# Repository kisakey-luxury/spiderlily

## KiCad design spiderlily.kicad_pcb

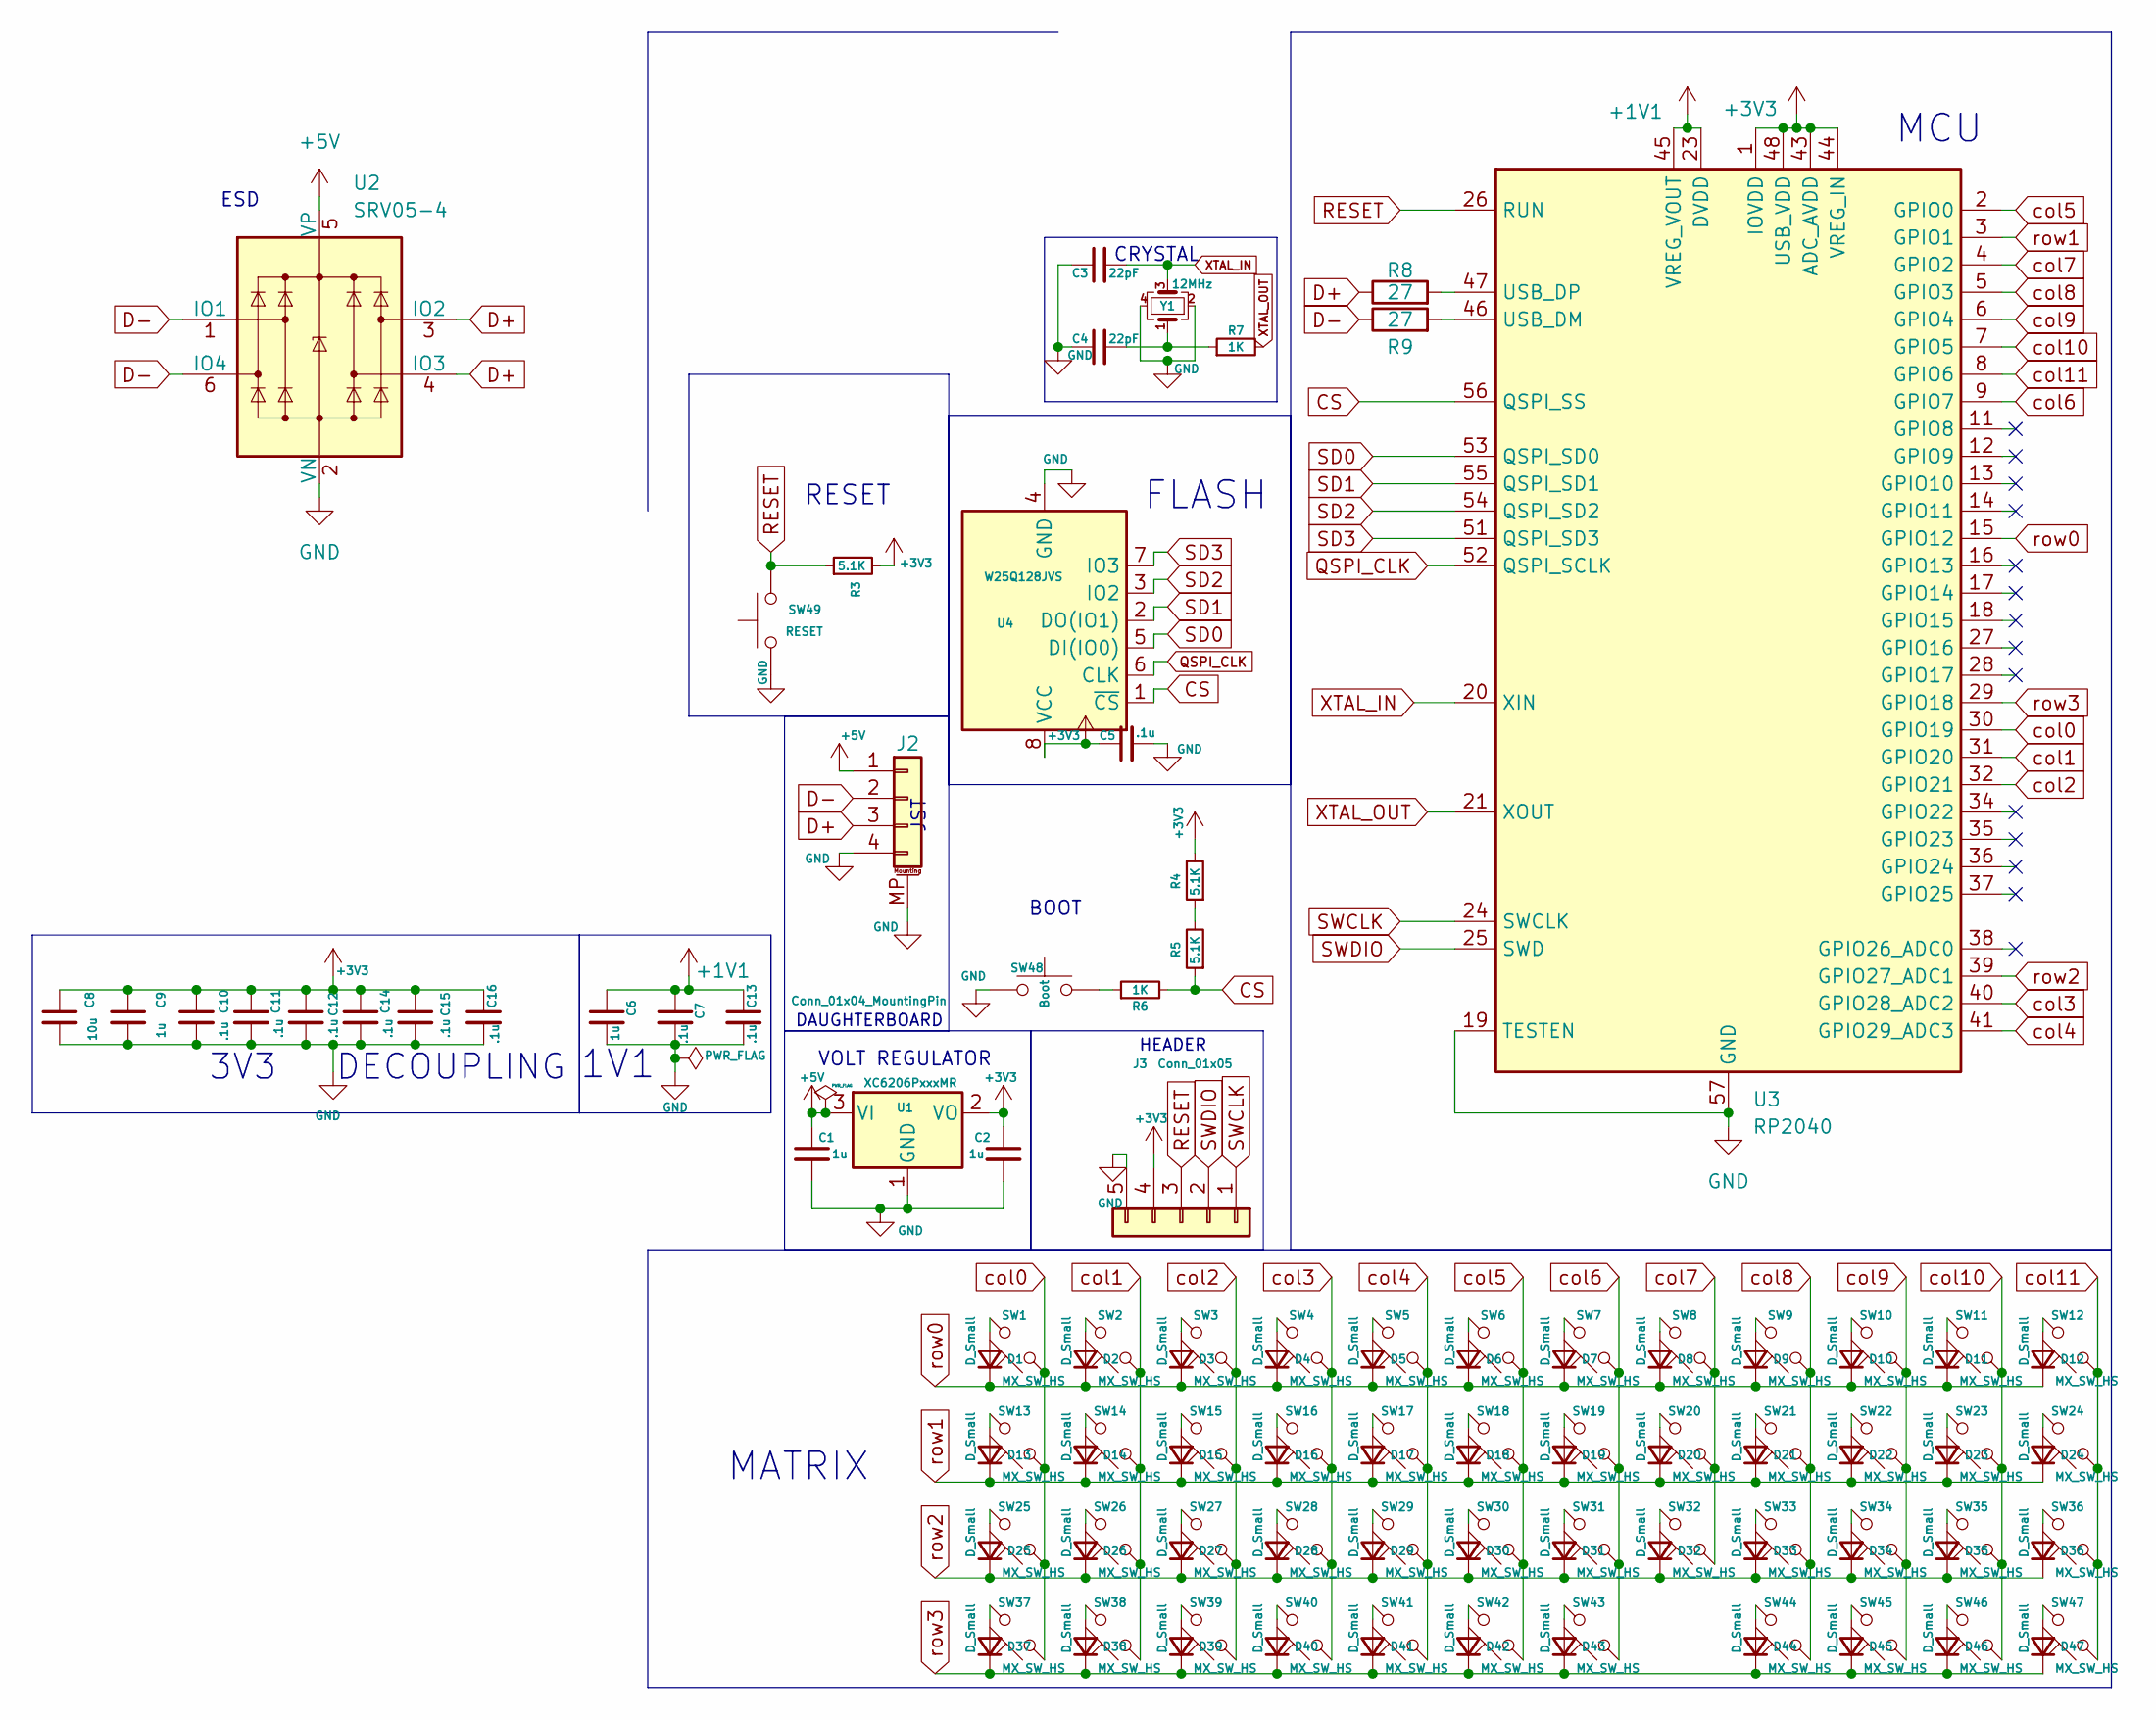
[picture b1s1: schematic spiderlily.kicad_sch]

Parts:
C1, C2, C6, C9: 1u; C_0402_1005Metric; LCSC C52923
C3: 22pF; C_0402_1005Metric; LCSC C1555
C4: 22pF; R_0402_1005Metric; LCSC C1555
C5, C7, C10, C11, C12, C13, C14, C15, C16: .1u; C_0402_1005Metric; LCSC C1525
C8: 10u; C_0402_1005Metric; LCSC C15525
D1, D2, D3, D4, D5, D6, D7, D8, D9, D10, D11, D12, D13, D14, D15, D16, D17, D18, D19, D20, D21, D22, D23, D24, D25, D26, D27, D28, D29, D30, D31, D32, D33, D34, D35, D36, D37, D38, D39, D40, D41, D42, D43, D44, D45, D46, D47: D_Small; D_SOD-123; LCSC C81598
J2: Conn_01x04_MountingPin; JST_SH_SM04B-SRSS-TB_1x04-1MP_P1.00mm_Horizontal; LCSC C3029343
J3: Conn_01x05; PinHeader_1x05_P2.54mm_Vertical
R3, R4, R5: 5.1K; R_0402_1005Metric; LCSC C25905
R6, R7: 1K; R_0402_1005Metric; LCSC C11702
R8, R9: 27; R_0402_1005Metric; LCSC C25100
SW1, SW2, SW3, SW4, SW5, SW6, SW7, SW8, SW9, SW10, SW11, SW12, SW14, SW15, SW16, SW17, SW18, SW19, SW20, SW21, SW22, SW23, SW26, SW27, SW28, SW29, SW30, SW31, SW32, SW33, SW34, SW35, SW36, SW37, SW38, SW39, SW40, SW44, SW45, SW46, SW47: MX_SW_HS; SW_MX_HS_CPG151101S11_1u; LCSC C41430893
SW13, SW42: MX_SW_HS; SW_MX_HS_CPG151101S11_1.25u; LCSC C41430893
SW24: MX_SW_HS; SW_MX_HS_CPG151101S11_1.5u; LCSC C41430893
SW25, SW41, SW43: MX_SW_HS; SW_MX_HS_CPG151101S11_1.75u; LCSC C41430893
SW48: Boot; SW_SPST_TL3342; LCSC C318884
SW49: RESET; SW_SPST_TL3342; LCSC C318884
U1: XC6206PxxxMR; SOT-23-3; LCSC C5446
U2: SRV05-4; SOT-23-6-routable; LCSC C85364
U3: RP2040; QFN-56-1EP_7x7mm_P0.4mm_EP3.2x3.2mm; LCSC C2040
U4: W25Q128JVS; SOIC-8_5.23x5.23mm_P1.27mm; LCSC C97521
Y1: 12MHz; Crystal_SMD_3225-4Pin_3.2x2.5mm; LCSC C9002

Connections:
+1V1: C6.1, C7.1, C13.1, U3.23 (DVDD), U3.45 (VREG_VOUT), U3.50 (DVDD)
+3V3: C2.1, C5.1, C8.1, C9.1, C10.1, C11.1, C12.1, C14.1, C15.1, C16.1, J3.4, R3.2, R4.2, U1.2 (VO), U3.1 (IOVDD), U3.10 (IOVDD), U3.22 (IOVDD), U3.33 (IOVDD), U3.42 (IOVDD), U3.43 (ADC_AVDD), U3.44 (VREG_IN), U3.48 (USB_VDD), U3.49 (IOVDD), U4.8 (VCC)
+5V: C1.1, J2.1, U1.3 (VI), U2.5 (VP)
CS: R5.1, R6.2, U3.56 (QSPI_SS), U4.1 (~CS)
D+: J2.3, R8.1, U2.3 (IO2), U2.4 (IO3)
D-: J2.2, R9.1, U2.1 (IO1), U2.6 (IO4)
GND: C1.2, C2.2, C3.1, C4.1, C5.2, C6.2, C7.2, C8.2, C9.2, C10.2, C11.2, C12.2, C13.2, C14.2, C15.2, C16.2, J2.4, J2.MP (MountPin), J3.5, SW48.1, SW49.1, U1.1 (GND), U2.2 (VN), U3.19 (TESTEN), U3.57 (GND), U4.4 (GND), Y1.2, Y1.4
unnamed: C4.2, R7.1, Y1.1
unnamed: D1.2 (A), SW1.2
unnamed: D2.2 (A), SW2.2
unnamed: D3.2 (A), SW3.2
unnamed: D4.2 (A), SW4.2
unnamed: D5.2 (A), SW5.2
unnamed: D6.2 (A), SW6.2
unnamed: D7.2 (A), SW7.2
unnamed: D8.2 (A), SW8.2
unnamed: D9.2 (A), SW9.2
unnamed: D10.2 (A), SW10.2
unnamed: D11.2 (A), SW11.2
unnamed: D12.2 (A), SW12.2
unnamed: D13.2 (A), SW13.2
unnamed: D14.2 (A), SW14.2
unnamed: D15.2 (A), SW15.2
unnamed: D16.2 (A), SW16.2
unnamed: D17.2 (A), SW17.2
unnamed: D18.2 (A), SW18.2
unnamed: D19.2 (A), SW19.2
unnamed: D20.2 (A), SW20.2
unnamed: D21.2 (A), SW21.2
unnamed: D22.2 (A), SW22.2
unnamed: D23.2 (A), SW23.2
unnamed: D24.2 (A), SW24.2
unnamed: D25.2 (A), SW25.2
unnamed: D26.2 (A), SW26.2
unnamed: D27.2 (A), SW27.2
unnamed: D28.2 (A), SW28.2
unnamed: D29.2 (A), SW29.2
unnamed: D30.2 (A), SW30.2
unnamed: D31.2 (A), SW31.2
unnamed: D32.2 (A), SW32.2
unnamed: D33.2 (A), SW33.2
unnamed: D34.2 (A), SW34.2
unnamed: D35.2 (A), SW35.2
unnamed: D36.2 (A), SW36.2
unnamed: D37.2 (A), SW37.2
unnamed: D38.2 (A), SW38.2
unnamed: D39.2 (A), SW39.2
unnamed: D40.2 (A), SW40.2
unnamed: D41.2 (A), SW41.2
unnamed: D42.2 (A), SW42.2
unnamed: D43.2 (A), SW43.2
unnamed: D44.2 (A), SW44.2
unnamed: D45.2 (A), SW45.2
unnamed: D46.2 (A), SW46.2
unnamed: D47.2 (A), SW47.2
unnamed: R4.1, R5.2
unnamed: R6.1, SW48.2
unnamed: R9.2, U3.46 (USB_DM)
unnamed: R8.2, U3.47 (USB_DP)
QSPI_CLK: U3.52 (QSPI_SCLK), U4.6 (CLK)
RESET: J3.3, R3.1, SW49.2, U3.26 (RUN)
SD0: U3.53 (QSPI_SD0), U4.5 (DI(IO0))
SD1: U3.55 (QSPI_SD1), U4.2 (DO(IO1))
SD2: U3.54 (QSPI_SD2), U4.3 (IO2)
SD3: U3.51 (QSPI_SD3), U4.7 (IO3)
SWCLK: J3.1, U3.24 (SWCLK)
SWDIO: J3.2, U3.25 (SWD)
XTAL_IN: C3.2, U3.20 (XIN), Y1.3
XTAL_OUT: R7.2, U3.21 (XOUT)
col0: SW1.1, SW13.1, SW25.1, SW37.1, U3.30 (GPIO19)
col1: SW2.1, SW14.1, SW26.1, SW38.1, U3.31 (GPIO20)
col2: SW3.1, SW15.1, SW27.1, SW39.1, U3.32 (GPIO21)
col3: SW4.1, SW16.1, SW28.1, SW40.1, U3.40 (GPIO28_ADC2)
col4: SW5.1, SW17.1, SW29.1, SW41.1, U3.41 (GPIO29_ADC3)
col5: SW6.1, SW18.1, SW30.1, SW42.1, U3.2 (GPIO0)
col6: SW7.1, SW19.1, SW31.1, SW43.1, U3.9 (GPIO7)
col7: SW8.1, SW20.1, SW32.1, U3.4 (GPIO2)
col8: SW9.1, SW21.1, SW33.1, SW44.1, U3.5 (GPIO3)
col9: SW10.1, SW22.1, SW34.1, SW45.1, U3.6 (GPIO4)
col10: SW11.1, SW23.1, SW35.1, SW46.1, U3.7 (GPIO5)
col11: SW12.1, SW24.1, SW36.1, SW47.1, U3.8 (GPIO6)
row0: D1.1 (K), D2.1 (K), D3.1 (K), D4.1 (K), D5.1 (K), D6.1 (K), D7.1 (K), D8.1 (K), D9.1 (K), D10.1 (K), D11.1 (K), D12.1 (K), U3.15 (GPIO12)
row1: D13.1 (K), D14.1 (K), D15.1 (K), D16.1 (K), D17.1 (K), D18.1 (K), D19.1 (K), D20.1 (K), D21.1 (K), D22.1 (K), D23.1 (K), D24.1 (K), U3.3 (GPIO1)
row2: D25.1 (K), D26.1 (K), D27.1 (K), D28.1 (K), D29.1 (K), D30.1 (K), D31.1 (K), D32.1 (K), D33.1 (K), D34.1 (K), D35.1 (K), D36.1 (K), U3.39 (GPIO27_ADC1)
row3: D37.1 (K), D38.1 (K), D39.1 (K), D40.1 (K), D41.1 (K), D42.1 (K), D43.1 (K), D44.1 (K), D45.1 (K), D46.1 (K), D47.1 (K), U3.29 (GPIO18)

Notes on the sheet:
CRYSTAL
3V3
HEADER
VOLT REGULATOR
DECOUPLING
MATRIX
JST
MCU
ESD
BOOT
RESET
FLASH
1V1
DAUGHTERBOARD

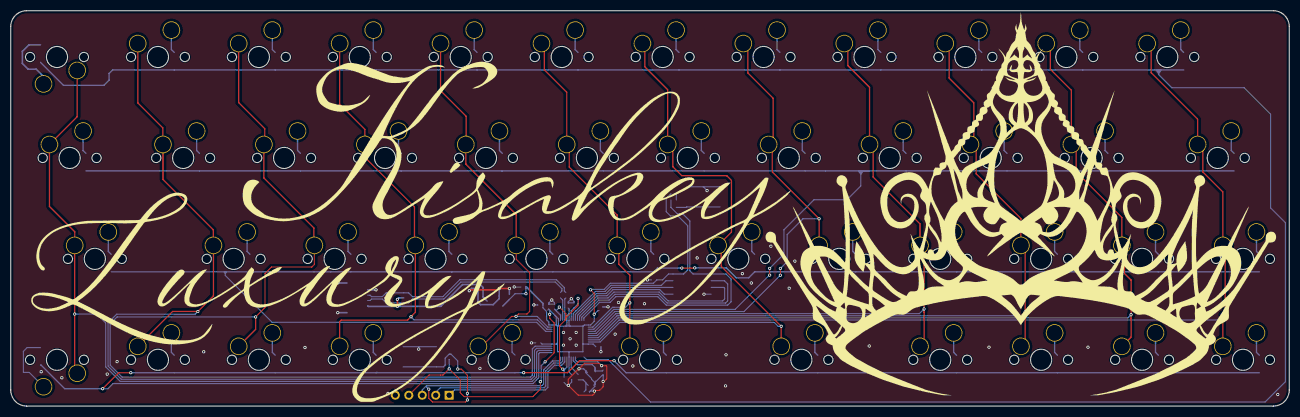
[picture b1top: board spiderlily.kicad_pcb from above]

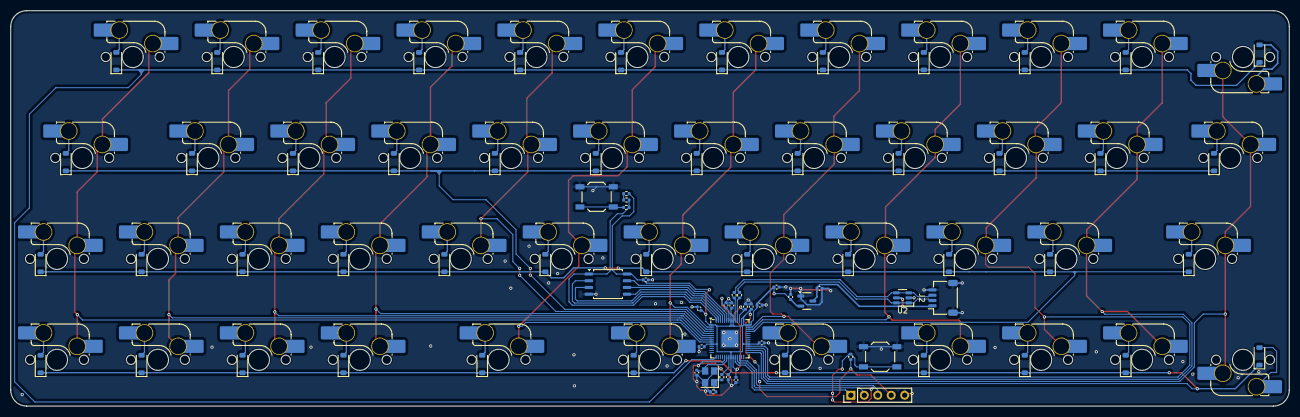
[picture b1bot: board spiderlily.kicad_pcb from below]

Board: 2 copper layers, 241.3 x 74.6 mm, 126 parts (126 on the bottom side), 85 nets.

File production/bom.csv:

Designator,Footprint,Quantity,Value,LCSC Part #
"C1, C2, C6, C9",0402,4,1u,C52923
"C10, C11, C12, C13, C14, C15, C16, C5, C7",0402,9,.1u,C1525
"C3, C4",0402,2,22pF,C1555
C8,0402,1,10u,C15525
"D1, D10, D11, D12, D13, D14, D15, D16, D17, D18, D19, D2, D20, D21, D22, D23, D24, D25, D26, D27, D28, D29, D3, D30, D31, D32, D33, D34, D35, D36, D37, D38, D39, D4, D40, D41, D42, D43, D44, D45, D46, D47, D5, D6, D7, D8, D9",D_SOD-123,47,D_Small,C81598
J2,Molex_Pico-EZmate_78171-0004_1x04-1MP_P1.20mm_Vertical,1,Conn_01x04_MountingPin,C3029343
J3,PinHeader_1x05_P2.54mm_Vertical,1,Conn_01x05,
"R3, R4, R5",0402,3,5.1K,C25905
"R6, R7",0402,2,1K,C11702
"R8, R9",0402,2,27,C25100
"SW1, SW10, SW11, SW12, SW14, SW15, SW16, SW17, SW18, SW19, SW2, SW20, SW21, SW22, SW23, SW26, SW27, SW28, SW29, SW3, SW30, SW31, SW32, SW33, SW34, SW35, SW36, SW37, SW38, SW39, SW4, SW40, SW44, SW45, SW46, SW47, SW5, SW6, SW7, SW8, SW9",SW_MX_HS_CPG151101S11_1u,41,MX_SW_HS,C41430893
"SW13, SW42",SW_MX_HS_CPG151101S11_1.25u,2,MX_SW_HS,C41430893
SW24,SW_MX_HS_CPG151101S11_1.5u,1,MX_SW_HS,C41430893
"SW25, SW41, SW43",SW_MX_HS_CPG151101S11_1.75u,3,MX_SW_HS,C41430893
SW48,SW_SPST_TL3342,1,Boot,C318884
SW49,SW_SPST_TL3342,1,RESET,C318884
U1,SOT-23-3,1,XC6206PxxxMR,C5446
U2,SOT-23-6-routable,1,SRV05-4,C85364
U3,QFN-56-1EP_7x7mm_P0.4mm_EP3.2x3.2mm,1,RP2040,C2040
U4,SOIC-8_5.23x5.23mm_P1.27mm,1,W25Q128JVS,C97521
Y1,Crystal_SMD_3225-4Pin_3.2x2.5mm,1,12MHz,C9002

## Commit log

2025-11-08 push
2025-11-11 few changes
2025-11-13 parts list, minor changes, logo
2025-11-24 fixing UDB connection
2025-11-24 updated ezmate to jst sh, fixed oritentation and clearence issues
2025-11-25 changed trace T angles to triangle polygons, readjusted bottom capacitors to leave 2mm gap from edge of pcb
2025-12-01 added GND vias liberally
2025-12-01 production fabrication files
